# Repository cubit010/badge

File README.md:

# Cubadge
A Pcb badge with built in NFC functions, with i2c broken out for access with external microcontrollers

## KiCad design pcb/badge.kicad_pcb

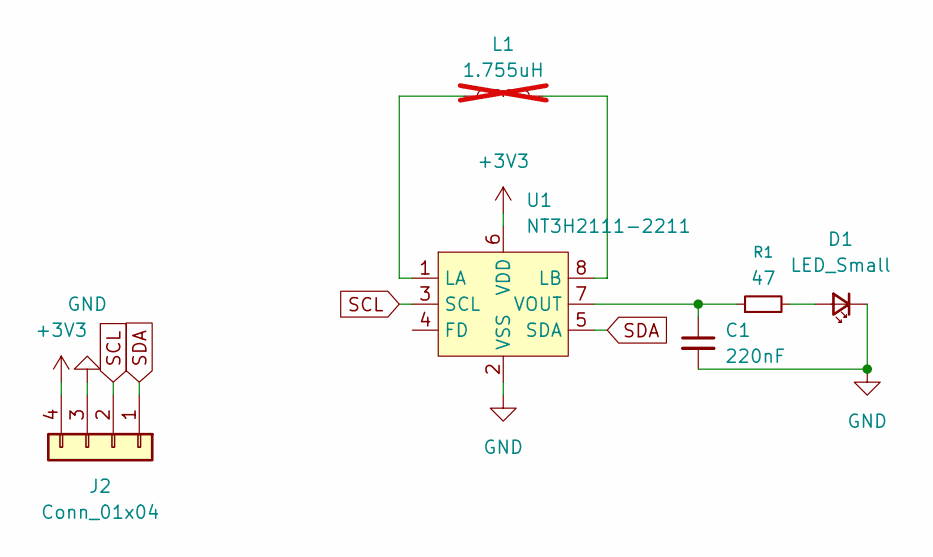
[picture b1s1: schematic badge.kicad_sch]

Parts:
C1: 220nF; C_0402_1005Metric
D1: LED_Small; LED_0603_1608Metric
J2: Conn_01x04; PinHeader_1x04_P2.54mm_Vertical
L1: 1.755uH; nfc-coil-2; not fitted
R1: 47; R_0603_1608Metric
U1: NT3H2111-2211; NT3H2111W0FHKH

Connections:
+3V3: J2.4, U1.6 (VDD)
GND: C1.2, D1.1 (K), J2.3, U1.2 (VSS)
unnamed: D1.2 (A), R1.2
unnamed: L1.1, U1.1 (LA)
unnamed: L1.2, U1.8 (LB)
unnamed: C1.1, R1.1, U1.7 (VOUT)
SCL: J2.2, U1.3 (SCL)
SDA: J2.1, U1.5 (SDA)

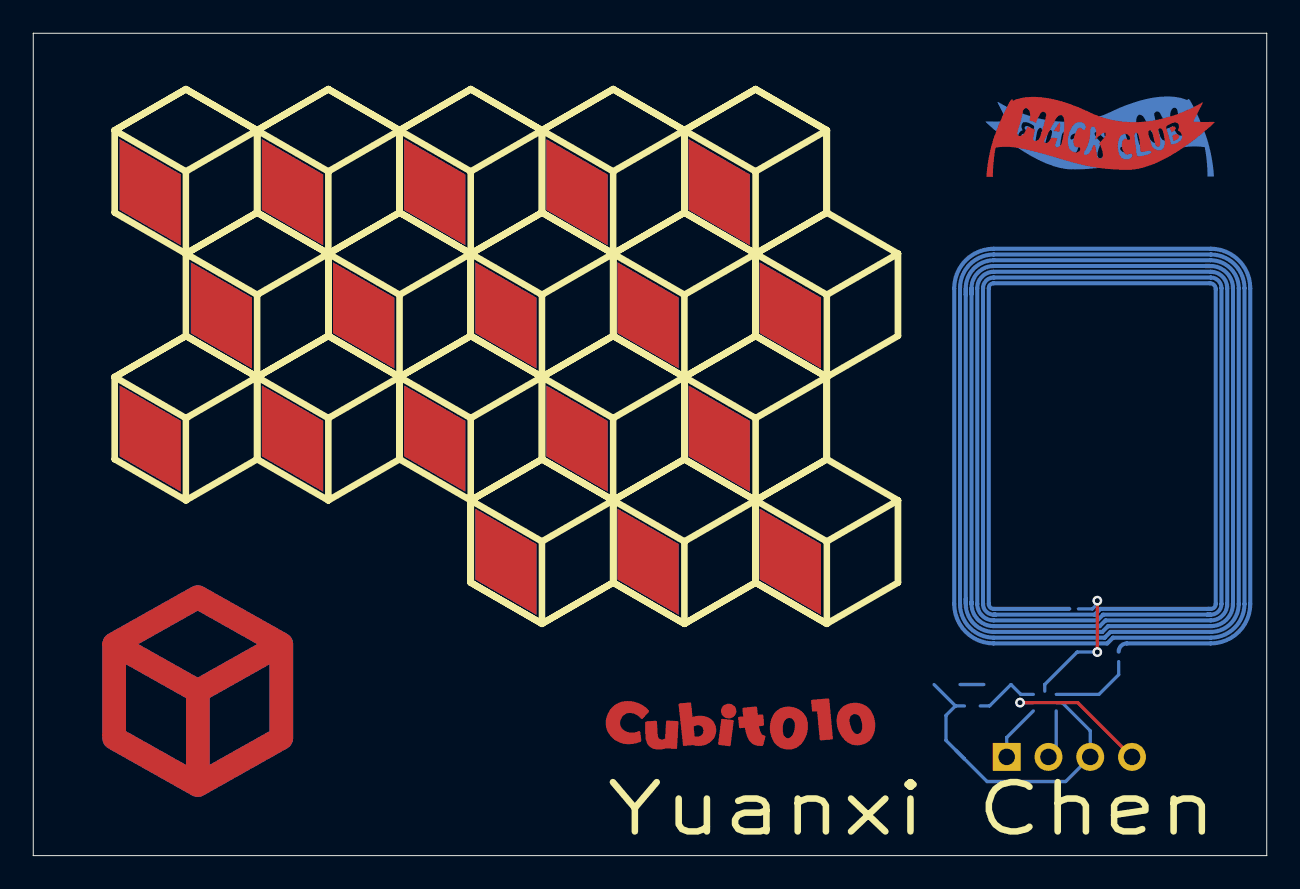
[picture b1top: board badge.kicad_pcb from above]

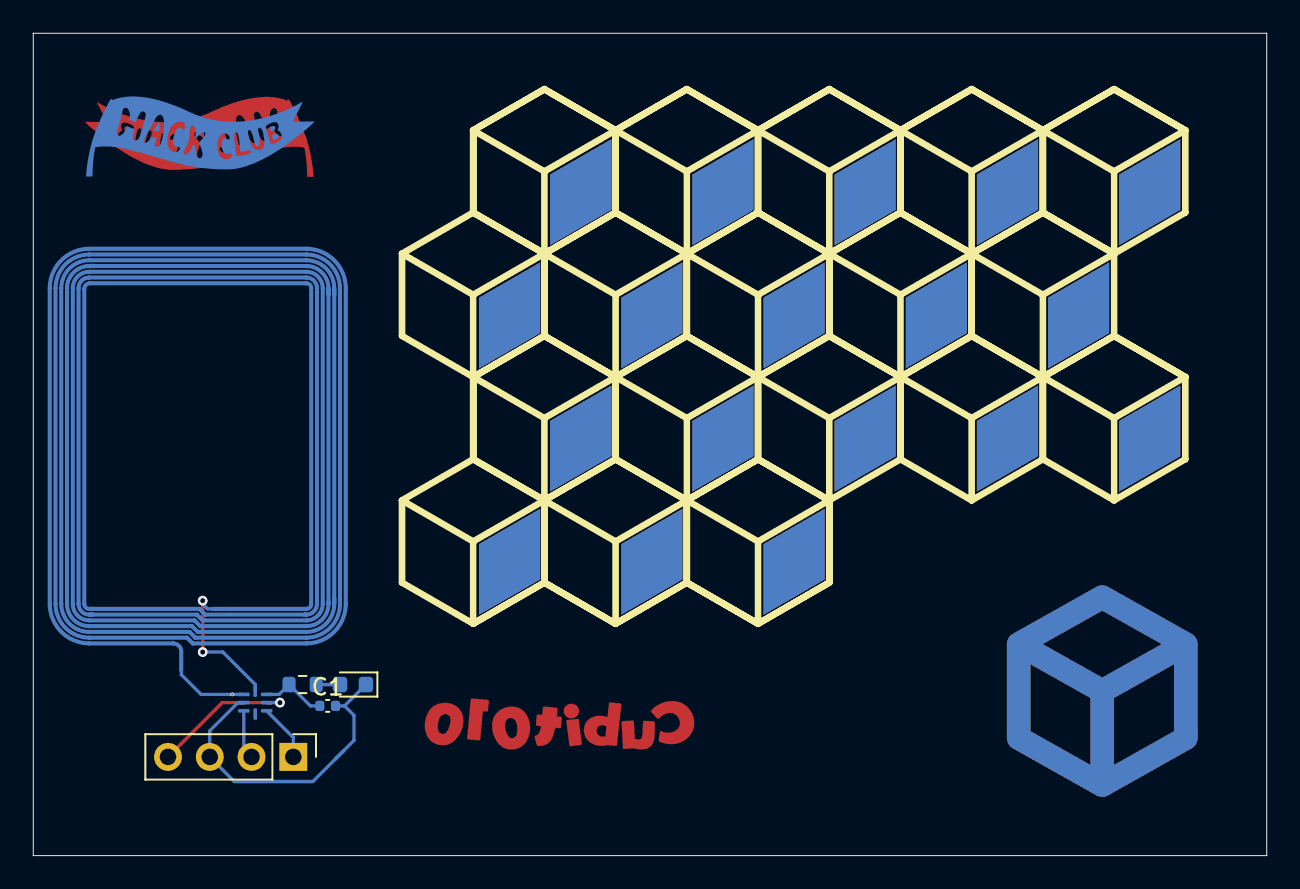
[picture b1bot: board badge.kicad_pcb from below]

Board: 2 copper layers, 75.0 x 50.0 mm, 6 parts (6 on the bottom side), 8 nets.

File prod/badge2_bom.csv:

Designator,Footprint,Quantity,Value,LCSC Part #
C1,0402,1,220nF,
D1,0603,1,LED_Small,
J2,PinHeader_1x04_P2.54mm_Vertical,1,Conn_01x04,
L1,nfc-coil-2,1,1.755uH,
R1,0603,1,47,
U1,NT3H2111W0FHKH,1,NT3H2111-2211,
